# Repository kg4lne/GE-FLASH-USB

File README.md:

GE-Flash-USB X2212/X2444 EPROM Programmer
=========================================

This archive contains all the CAD and firmware files necessary to build the
GE-Flash-USB EPROM programmer for use with the GE-Flash programming software
by KG4LNE. GE-Flash is a complete solution for programming vintage GE Phoenix,
Delta and Ranger VHF/UHF commercial radios. For more information, please visit
the website at http://www.rtzaudio.com/kg4lne for additional information.

This package includes all PCB CAD files and firmware C source code. All PCB CAD
files are in Cadsoft Eagle v6.4.0 format. The source code for the AT90USB firmware
was developed in Atmel Studio 6.1 and was originally adapted from the USBKEY sample
provided by Atmel. I modified this from a mass storage device into to a simple
read/write USB device. The simple USB device can be accessed on Windows 7/8 via
the built-in generic WinUSB interface that ships with Windows.

You will need to install and configure your GE-Flash-USB programmer device to
communicate with WinUSB just like any other device though. The GE-Flash-USB driver
install and INF files are located on my website and are included in the 
GE-Flash application installer also. Be sure and have the INF and other driver
files on your machine (or install the GE-Flash application first). You can let
Windows search the GE-Flash program files application directory for the INF
file as well.

Note the BOM files for the programmer PCB are located in the project BOM 
subdirectory, here you'll also find an order upload file
"GEF-USB-B_OrderUploadDigiKey.csv" that can be uploaded to Digikey.
Upload the parts order file using the Digikey BOM manager in your account,
this will preload an order with all parts needed to build the PCB. 

Enjoy!

KG4LNE

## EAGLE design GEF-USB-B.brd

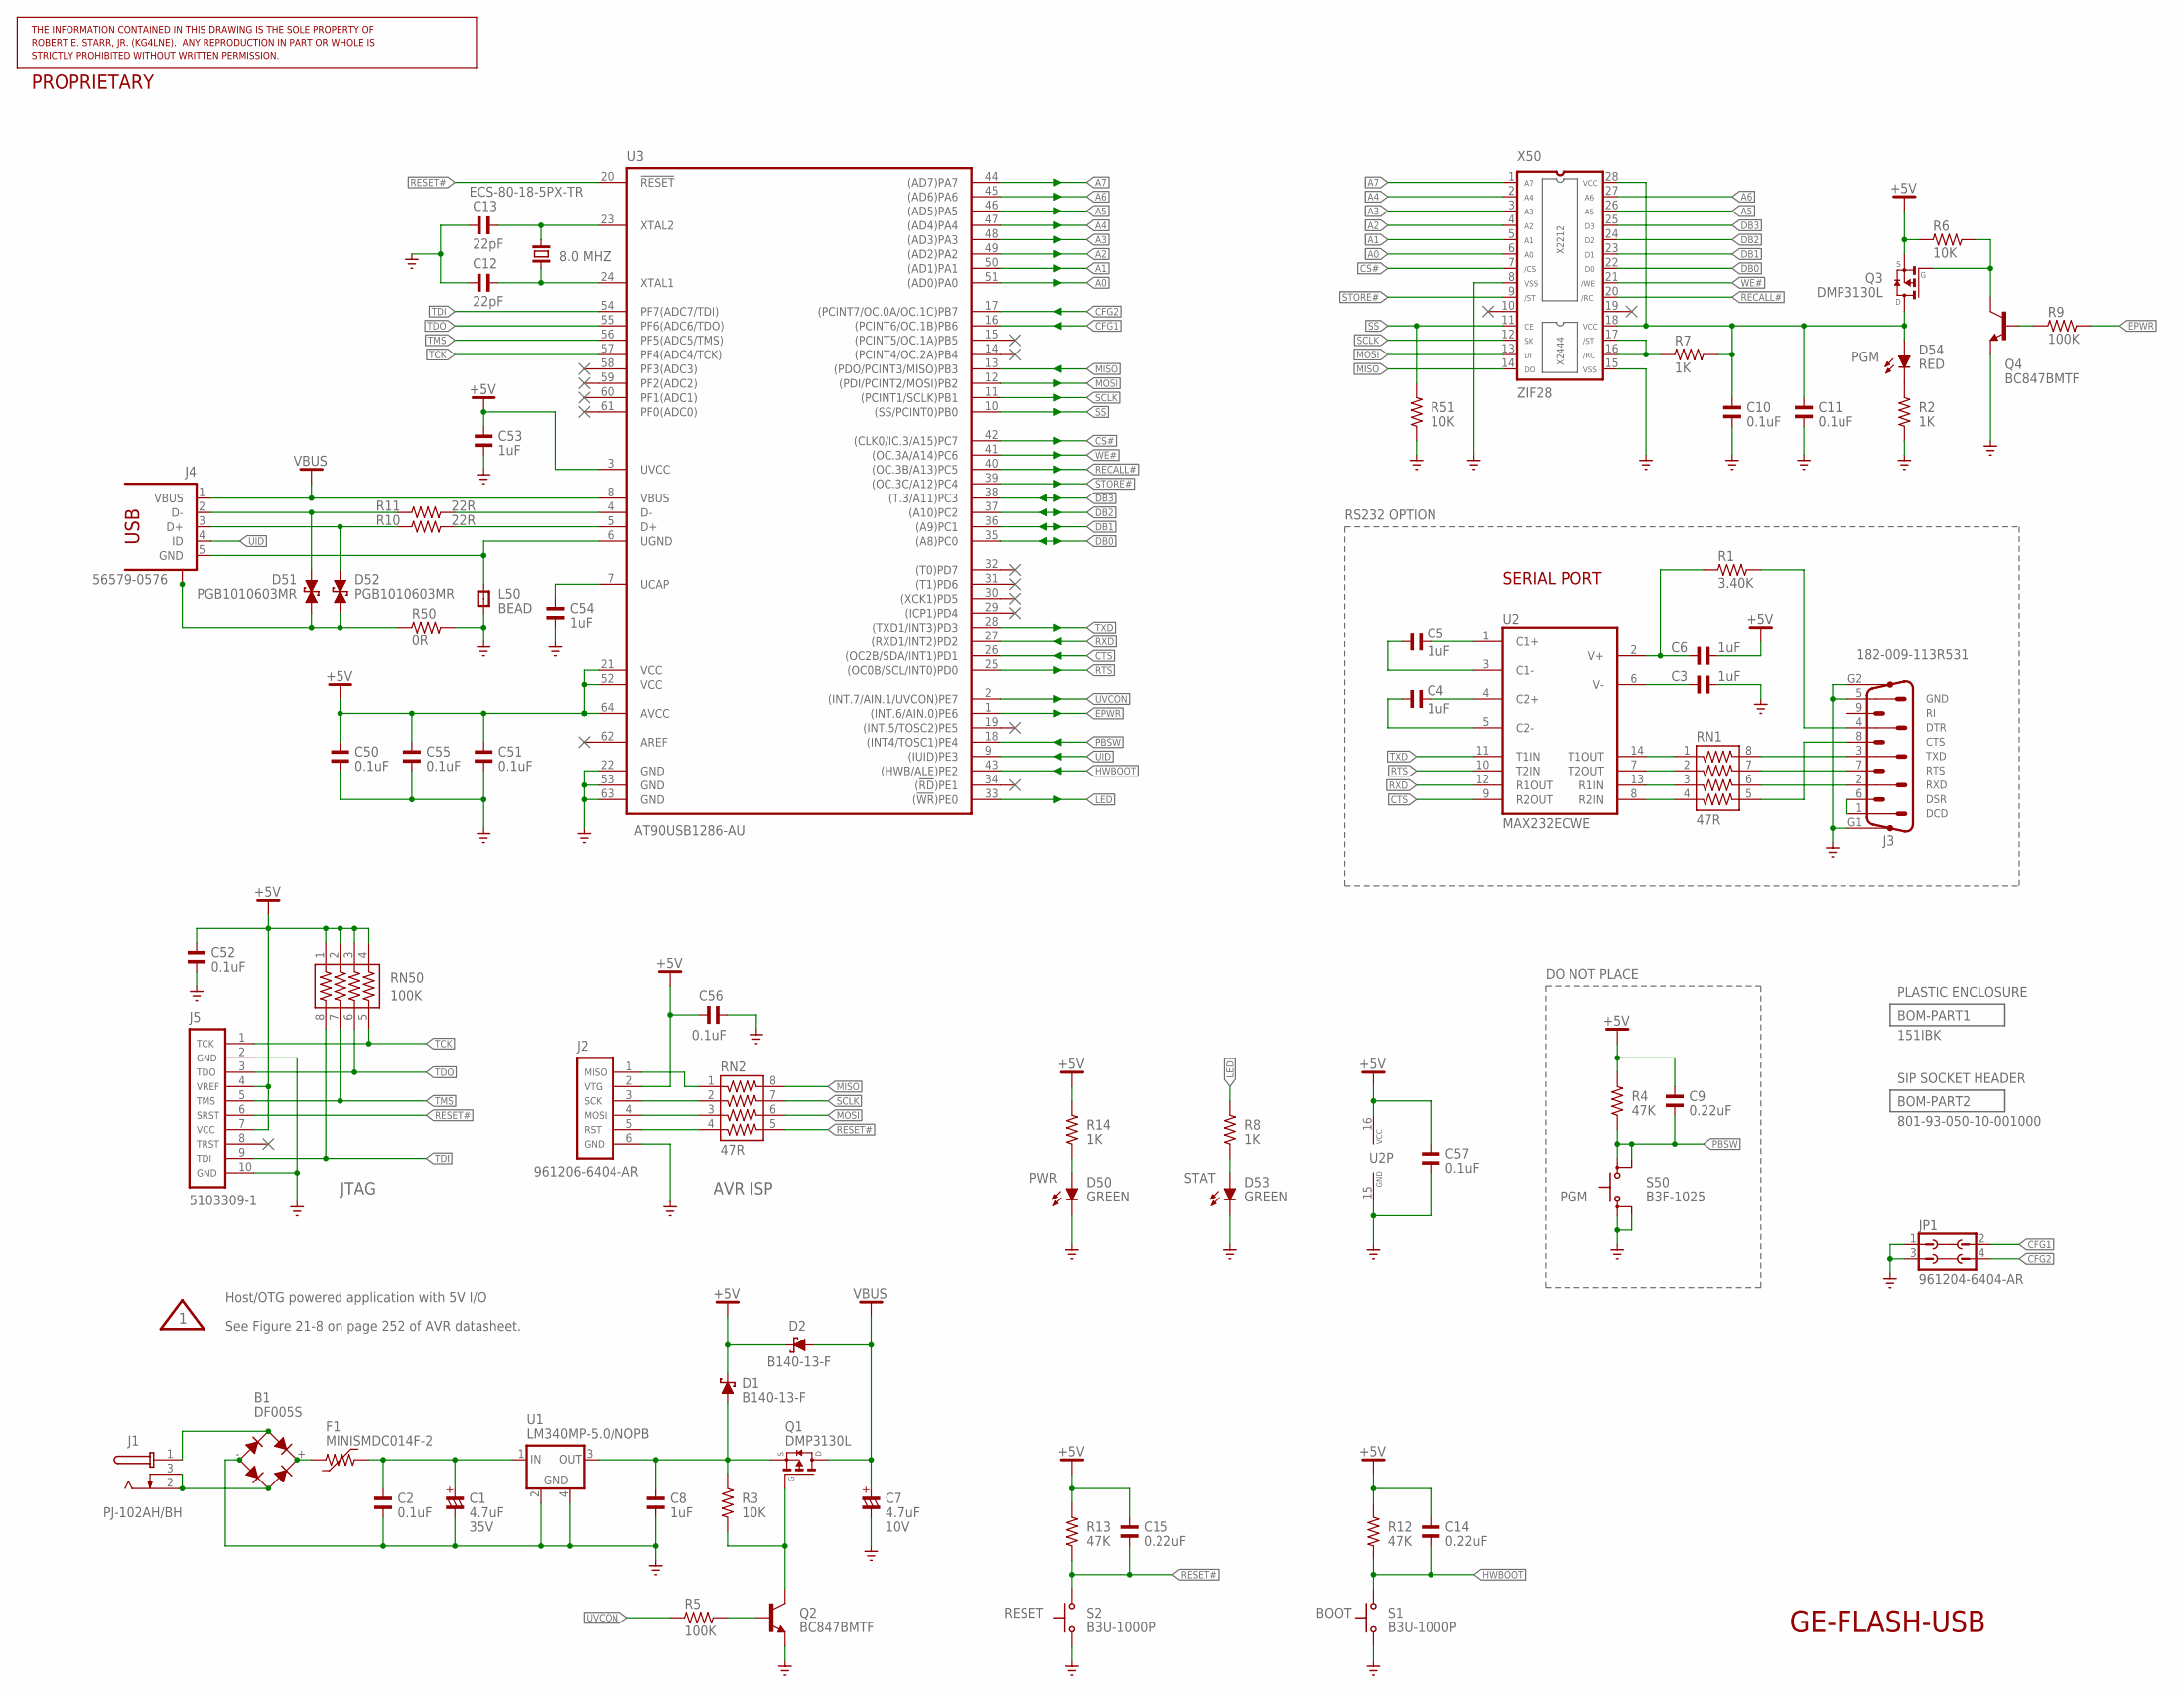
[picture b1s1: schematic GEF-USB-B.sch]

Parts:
B1: DF005S; DF-S; PARTNO DF005S
C1: 4.7uF; C7343/T; PARTNO TAJD475M035RNJ
C2, C10, C11, C50, C51, C52, C55, C56, C57: 0.1uF; C0805; PARTNO GCM21BR72A104KA37L
C3, C4, C5, C6, C8, C53, C54: 1uF; C0805; PARTNO GCM21BR71E105KA56L
C7: 4.7uF; C3528/T; PARTNO TAJB475K010RNJ
C9, C14, C15: 0.22uF; C0805; PARTNO GCM21BR71H224KA37L
C12, C13: 22pF; C0805; PARTNO GRM2195C2A220JZ01D
D1, D2: B140-13-F; SMA; PARTNO B140-13-F
D50, D53: GREEN; LED3MM; PARTNO TLHG4405
D51, D52: PGB1010603MR; PGB-0603; PARTNO PGB1010603MR
D54: RED; LED3MM; PARTNO TLHR4405
F1: MINISMDC014F-2; F1812; PARTNO MINISMDC014F-2
J1: PJ-102AH/BH; PJ-102XH; PARTNO PJ-102AH
J2: 961206-6404-AR; HDR-MA03-2; PARTNO 961206-6404-AR
J3: 182-009-113R531; NC182M9; PARTNO 182-009-113R531
J4: 56579-0576; PARTNO 56579-0576
J5: 5103309-1; HDR-5103309-1; PARTNO 5103309-1
JP1: 961204-6404-AR; JP2Q; PARTNO 961204-6404-AR
L50: BEAD; L0805; PARTNO BLM21PG221SN1D
Q1, Q3: DMP3130L; SOT23; PARTNO DMP3130L
Q2, Q4: BC847BMTF; SOT23; PARTNO BC847BMTF
R1: 3.40K; R0805; PARTNO ERJ-6ENF3401V
R2, R7, R8, R14: 1K; R0805; PARTNO ERJ-6ENF1001V
R3, R6, R51: 10K; R0805; PARTNO ERJ-6ENF1022V
R4, R12, R13: 47K; R0805; PARTNO ERJ-6ENF4702V
R5, R9: 100K; R0805; PARTNO ERJ-6ENF1003V
R10, R11: 22R; R0805; PARTNO ERJ-6ENF22R1V
R50: 0R; R0805; PARTNO ERJ-6GEY0R00V
RN1, RN2: 47R; 744-8; PARTNO 744C083470JTR
RN50: 100K; 744-8; PARTNO 744C083104JPTR
S1, S2: B3U-1000P; PARTNO B3U-1000P
S50: B3F-1025; B3F-10XX-B; PARTNO B3F-1025
U1: LM340MP-5.0/NOPB; SOT223; PARTNO LM340MP-5.0/NOPB
U2: MAX232ECWE; SO16W; PARTNO MAX232ECWE+
U3: AT90USB1286-AU; TQFP64A; PARTNO AT90USB1286-AU
X50: ZIF28; PARTNO 28-6554-11
Y1: 8.0 MHZ; HC49UP; PARTNO ECS-80-18-5PX-TR

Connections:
+5V: C6.1, C9.2, C14.2, C15.2, C50.1, C51.2, C52.1, C53.2, C55.1, C56.2, C57.1, D1.C, D2.C, J2.2, J5.4, J5.7, Q3.2 (S), R4.2, R6.1, R12.2, R13.2, R14.2, RN50.1, RN50.2, RN50.3, RN50.4, U2.16 (VCC), U3.3 (UVCC), U3.21 (VCC), U3.52 (VCC), U3.64 (AVCC)
A0: U3.51 ((AD0)PA0), X50.6
A1: U3.50 ((AD1)PA1), X50.5
A2: U3.49 ((AD2)PA2), X50.4
A3: U3.48 ((AD3)PA3), X50.3
A4: U3.47 ((AD4)PA4), X50.2
A5: U3.46 ((AD5)PA5), X50.26
A6: U3.45 ((AD6)PA6), X50.27
A7: U3.44 ((AD7)PA7), X50.1
CFG1: JP1.2, U3.16 ((PCINT6/OC.1B)PB6)
CFG2: JP1.4, U3.17 ((PCINT7/OC.0A/OC.1C)PB7)
CS#: U3.42 ((CLK0/IC.3/A15)PC7), X50.7
CTS: U2.9 (R2OUT), U3.26 ((OC2B/SDA/INT1)PD1)
DB0: U3.35 ((A8)PC0), X50.22
DB1: U3.36 ((A9)PC1), X50.23
DB2: U3.37 ((A10)PC2), X50.24
DB3: U3.38 ((T.3/A11)PC3), X50.25
EPWR: R9.2, U3.1 ((INT.6/AIN.0)PE6)
GND: B1.-, C1.-, C2.1, C3.1, C7.-, C8.2, C10.1, C11.1, C12.1, C13.1, C50.2, C51.1, C52.2, C53.1, C54.1, C55.2, C56.1, C57.2, D50.K (C), D53.K (C), J2.6, J3.5, J3.G1, J3.G2, J5.2, J5.10, JP1.1, JP1.3, L50.1, Q2.2 (E), Q4.2 (E), R2.1, R50.2, R51.1, S1.1, S2.1, S50.3, S50.4 (P1), U1.2 (GND), U1.4 (GND1), U2.15 (GND), U3.22 (GND), U3.53 (GND), U3.63 (GND), X50.8, X50.15
HWBOOT: C14.1, R12.1, S1.2 (S), U3.43 ((HWB/ALE)PE2)
LED: R8.2, U3.33 ((!WR!)PE0)
MISO: RN2.8, U3.13 ((PDO/PCINT3/MISO)PB3), X50.14
MOSI: RN2.6, U3.12 ((PDI/PCINT2/MOSI)PB2), X50.13
unnamed: J2.5, RN2.4
unnamed: B1.AC2 (A2), J1.2 (S), J1.3 (SS)
unnamed: R10.2, U3.5 (D+)
unnamed: D52.2, J4.3 (D+), R10.1
unnamed: R11.2, U3.4 (D-)
unnamed: D51.2, J4.2 (D-), R11.1
unnamed: C54.2, U3.7 (UCAP)
unnamed: D50.A, R14.1
unnamed: D51.1, D52.1, J4.S1, J4.S2, J4.S3, J4.S4, R50.1
unnamed: D53.A, R8.1
unnamed: Q1.1 (G), Q2.3 (C), R3.1
unnamed: Q2.1 (B), R5.2
unnamed: Q3.1 (G), Q4.3 (C), R6.2
unnamed: C10.2, C11.2, D54.A, Q3.3 (D), R7.2, X50.18, X50.28
unnamed: D54.K (C), R2.2
unnamed: J4.5 (GND), L50.2, U3.6 (UGND)
unnamed: J3.1, J3.6
unnamed: C1.+, C2.2, F1.2, U1.1 (IN)
unnamed: C8.1, D1.A, Q1.2 (S), R3.2, U1.3 (OUT)
unnamed: J3.2, RN1.6
unnamed: B1.+, F1.1
unnamed: B1.AC1 (A1), J1.1 (T)
unnamed: Q4.1 (B), R9.1
unnamed: C12.2, U3.24 (XTAL1), Y1.1
unnamed: J3.7, RN1.7
unnamed: C3.2, U2.6 (V-)
unnamed: C6.2, R1.1, U2.2 (V+)
unnamed: C13.2, U3.23 (XTAL2), Y1.2
unnamed: C4.1, U2.4 (C2+)
unnamed: C5.1, U2.1 (C1+)
unnamed: C4.2, U2.5 (C2-)
unnamed: C5.2, U2.3 (C1-)
unnamed: J3.8, RN1.5
unnamed: J3.3, RN1.8
unnamed: RN1.3, U2.13 (R1IN)
unnamed: RN1.1, U2.14 (T1OUT)
unnamed: RN1.4, U2.8 (R2IN)
unnamed: J3.4, R1.2
unnamed: RN1.2, U2.7 (T2OUT)
unnamed: J2.1, RN2.1
unnamed: J2.3, RN2.2
unnamed: J2.4, RN2.3
PBSW: C9.1, R4.1, S50.1 (S), S50.2 (S1), U3.18 ((INT4/TOSC1)PE4)
PU2: R7.1, X50.16, X50.17
RECALL#: U3.40 ((OC.3B/A13)PC5), X50.20
RESET#: C15.1, J5.6, R13.1, RN2.5, S2.2 (S), U3.20 (!RESET!)
RTS: U2.10 (T2IN), U3.25 ((OC0B/SCL/INT0)PD0)
RXD: U2.12 (R1OUT), U3.27 ((RXD1/INT2)PD2)
SCLK: RN2.7, U3.11 ((PCINT1/SCLK)PB1), X50.12
SS: R51.2, U3.10 ((SS/PCINT0)PB0), X50.11
STORE#: U3.39 ((OC.3C/A12)PC4), X50.9
TCK: J5.1, RN50.5, U3.57 (PF4(ADC4/TCK))
TDI: J5.9, RN50.8, U3.54 (PF7(ADC7/TDI))
TDO: J5.3, RN50.6, U3.55 (PF6(ADC6/TDO))
TMS: J5.5, RN50.7, U3.56 (PF5(ADC5/TMS))
TXD: U2.11 (T1IN), U3.28 ((TXD1/INT3)PD3)
UID: J4.4 (ID), U3.9 ((IUID)PE3)
UVCON: R5.1, U3.2 ((INT.7/AIN.1/UVCON)PE7)
VBUS: C7.+, D2.A, J4.1 (VBUS), Q1.3 (D), U3.8 (VBUS)
WE#: U3.41 ((OC.3A/A14)PC6), X50.21

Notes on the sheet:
AVR ISP
JTAG
See Figure 21-8 on page 252 of AVR datasheet.
Host/OTG powered application with 5V I/O
VCC
/WE
/ST
/RC
/CS
VSS
X2444
X2212
SERIAL PORT
DCD
DSR
RXD
RTS
TXD
CTS
DTR
GND
GE-FLASH-USB
DO NOT PLACE
RS232 OPTION

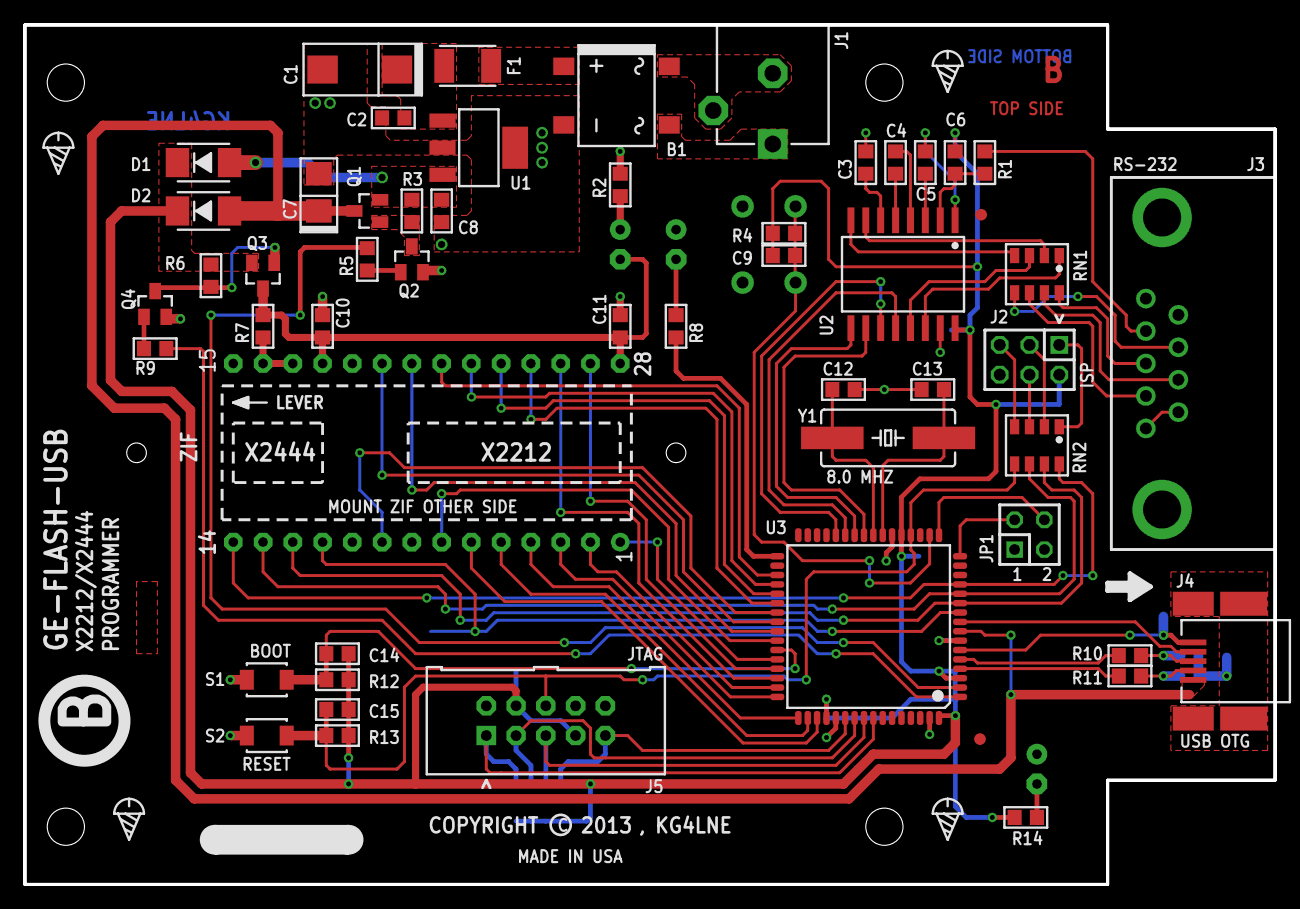
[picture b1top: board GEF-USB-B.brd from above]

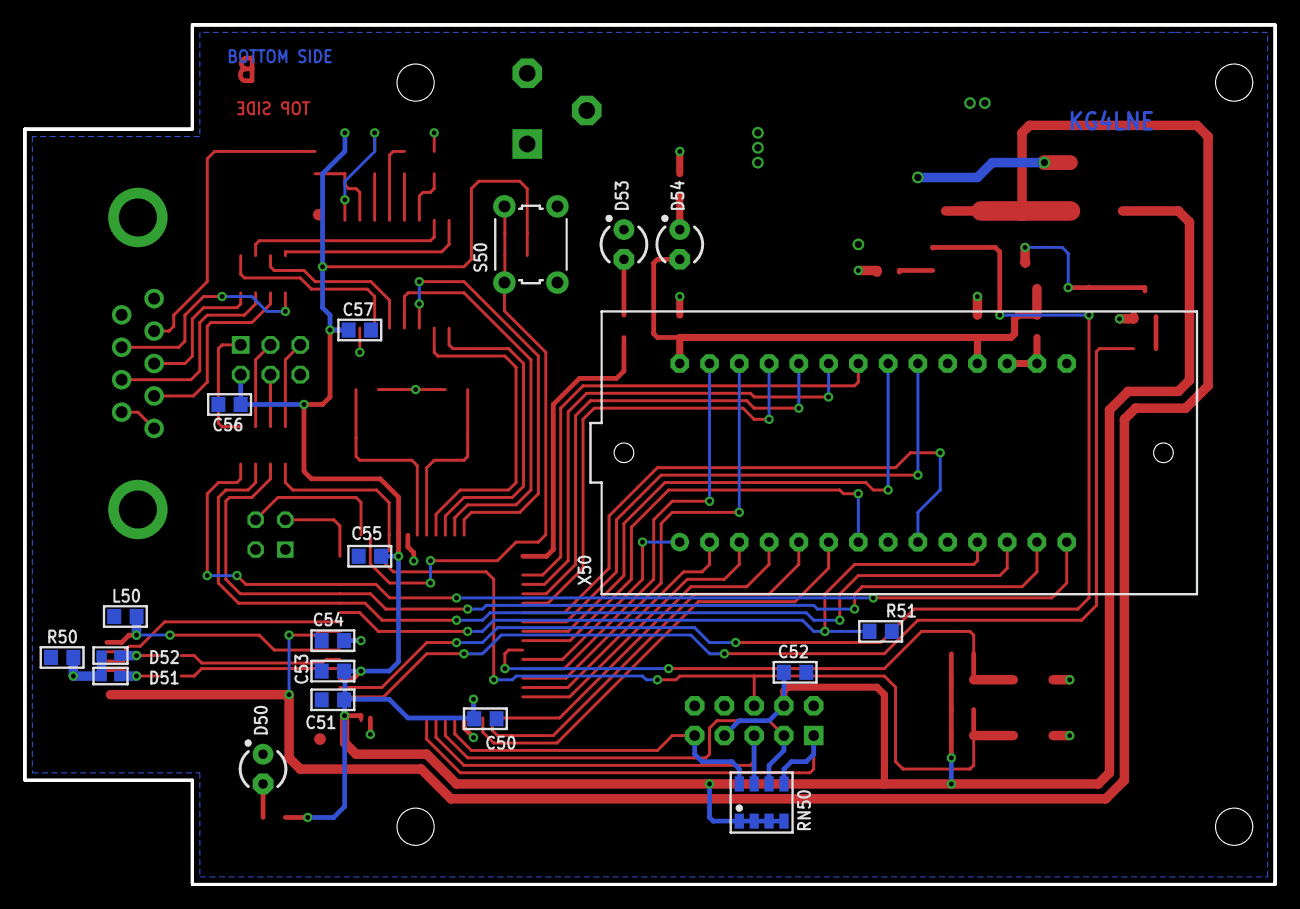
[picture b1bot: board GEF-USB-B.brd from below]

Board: 2 copper layers, 106.7 x 73.3 mm, 86 parts (19 on the bottom side), 83 nets.

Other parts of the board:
FABFRAME1: FAB_FRAME_ANSI-A
FABFRAME2: FAB_DOCFIELD_GENERIC
FEAT1, FEAT3, FEAT11, FEAT12: ICON_SCREW-S
FEAT2: PCBFEAT-MREV-076
FEAT4, FEAT9: G10
FEAT5, FEAT10: ICON_PIN1_A
FEAT6: ICON_ARROW-S
FEAT7: PCBFEAT-DATECODE-050R
FEAT8: PCBFEAT-REV-150
FEAT13: PCBFEAT-COPYRIGHT-050
FEAT14: FIELD_SCRIBBLE-1

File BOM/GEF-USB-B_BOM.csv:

Qty,Part References,Value,Package,Mfg Part Num,Mfg Name,VID,Vendor Part Num,Description,XREF
9,"C2, C10, C11, C50, C51, C52, C55, C56, C57",0.1uF,C0805,GCM21BR72A104KA37L,Murata Electronics,DK,490-4789-1-ND,CAP CER .1UF 100V X7R 0805,REF24
3,"C9(DNP), C14, C15",0.22uF,C0805,GCM21BR71H224KA37L,Murata Electronics,DK,490-4970-1-ND,CAP CER .22UF 50V X7R 0805,REF26
1,R50,0R,R0805,ERJ-6GEY0R00V,Panasonic - ECG,DK,P0.0ACT-ND,RES 0.0 OHM 1/8W 0805 SMD,REF29
4,"R2, R7, R8, R14",1K,R0805,ERJ-6ENF1001V,Panasonic - ECG,DK,P1.00KCCT-ND,RES 1.00K OHM 1/8W 1% 0805 SMD,REF30
7,"C3, C4, C5, C6, C8, C53, C54",1uF,C0805,GCM21BR71E105KA56L,Murata Electronics,DK,490-4785-1-ND,CAP CER 1UF 25V X7R 0805,REF27
1,R1,3.40K,R0805,ERJ-6ENF3401V,Panasonic - ECG,DK,P3.40KCCT-ND,RES 3.40K OHM 1/8W 1% 0805 SMD,REF31
1,C7,4.7uF,C3528/T,TAJB475K010RNJ,AVX Corporation,DK,478-3886-1-ND,CAP TANTALUM 4.7UF 10V 10% SMD,REF23
1,C1,4.7uF,C7343/T,TAJD475M035RNJ,AVX Corporation,DK,478-3934-1-ND,CAP TANTALUM 4.7UF 35V 20% SMD,REF22
1,Y1,8.0 MHZ,HC49UP,ECS-80-18-5PX-TR,ECS Inc,DK,XC1271CT-ND,CRYSTAL 8.00MHZ 18PF SMD,REF17
3,"R3, R6, R51",10K,R0805,ERJ-6ENF1022V,Panasonic - ECG,DK,P10.2KCCT-ND,RES 10.2K OHM 1/8W 1% 0805 SMD,REF32
2,"R10, R11",22R,R0805,ERJ-6ENF22R1V,Panasonic - ECG,DK,P22.1CCT-ND,RES 22.1 OHM 1/8W 1% 0805 SMD,REF33
2,"C12, C13",22pF,C0805,GRM2195C2A220JZ01D,Murata Electronics,DK,490-1591-1-ND,CAP CER 22PF 100V 5% C0G 0805,REF25
3,"R4(DNP), R12, R13",47K,R0805,ERJ-6ENF4702V,Panasonic - ECG,DK,P47.0KCCT-ND,RES 47.0K OHM 1/8W 1% 0805 SMD,REF35
2,"RN1, RN2",47R,744-8,744C083470JTR,CTS Resistor Products,DK,744C083470JPCT-ND,RES ARRAY 47 OHM 8TERM 4RES SMD,REF20
1,RN50,100K,744-8,744C083104JPTR,CTS Resistor Products,DK,744C083104JPCT-ND,RES ARRAY 100KOHM 8TERM 4RES SMD,REF21
2,"R5, R9",100K,R0805,ERJ-6ENF1003V,Panasonic - ECG,DK,P100KCCT-ND,RES 100K OHM 1/8W 1% 0805 SMD,REF36
1,BOM-PART1,151IBK,*,151IBK,Serpac,DK,SR151-IB-ND,PLASTIC ENCLOSURE 5.62X3.25X1.50 BLACK,REF39
1,J3,182-009-113R531,NC182M9,182-009-113R531,Norcomp Inc.,DK,182-09ME-ND,CONN DB9 MALE .318 R/A NICKEL,REF15
1,BOM-PART2,801-93-050-10-001000,*,801-93-050-10-001000,Mill-Max Mfg Corp,DK,ED7150-ND,SIP SOCKET 50 POS STRAIGHT PCB,REF40
1,J4,56579-0576,56579-0576,56579-0576,Molex Inc,DK,WM17122CT-ND,CONN RECEPT USB 5POS RT ANG SMD,REF14
1,JP1,961204-6404-AR,JP2Q,961204-6404-AR,3M,DK,3M9458-ND,CONN HEADER VERT DUAL 4POS GOLD,REF42
1,J2,961206-6404-AR,HDR-MA03-2,961206-6404-AR,3M,DK,3M9459-ND,CONN HEADER VERT DUAL 6POS GOLD,REF43
1,J5,5103309-1,HDR-5103309-1,5103309-1,Tyco Electronics,DK,A33160-ND,CONN HEADER LOPRO STR 10POS GOLD,REF16
1,U3,AT90USB1286-AU,TQFP64A,AT90USB1286-AU,Atmel,DK,AT90USB1286-AURCT-ND,MCU AVR 64K FLASH 16MHZ 64TQFP,REF2
1,S50(DNP),B3F-1025,B3F-10XX-B,B3F-1025,Omron Electronics Inc,DK,SW794-ND,SWITCH TACT 6MM 260GF H=5.0MM,REF11
2,"S1, S2",B3U-1000P,B3U-1000P,B3U-1000P,Omron Electronics Inc,DK,SW1020CT-ND,SWITCH TACT SPST W/O GND SMD,REF12
2,"D1, D2",B140-13-F,SMA,B140-13-F,Diodes Inc,DK,B140-FDICT-ND,DIODE SCHOTTKY 40V 1A SMA,REF38
2,"Q2, Q4",BC847BMTF,SOT23,BC847BMTF,Fairchild Semiconductor,DK,BC847BMTFCT-ND,TRANSISTOR NPN 45V 0.1A SOT23,REF4
1,L50,BEAD,L0805,BLM21PG221SN1D,Murata Electronics,DK,490-1054-1-ND,FERRITE CHIP 220 OHM 2000MA 0805,REF28
1,B1,DF005S,DF-S,DF005S,Fairchild Semiconductor,DK,DF005SCT-ND,DIODE BRIDGE 50V 1.5A 4-SDIP,REF5
2,"Q1, Q3",DMP3130L,SOT23,DMP3130L,Diodes Inc,DK,DMP3130LDICT-ND,MOSFET P-CH 30V 3.5A SOT-23,REF6
2,"D50, D53",GREEN,LED3MM,TLHG4405,Vishay Semiconductor,DK,751-1101-ND,LED 3MM GREEN 15MCD GAP ON GAP,REF10
1,U1,LM340MP-5.0/NOPB,SOT223,LM340MP-5.0/NOPB,National Semiconductor,DK,LM340MP-5.0/NOPBCT-ND,IC REG LDO 5V 1A SOT223,REF7
1,U2,MAX232ECWE,SO16W,MAX232ECWE+,Maxim Integrated Products,DK,MAX232ECWE+-ND,IC TXRX RS232 5V ESD-PROT 16SOIC,REF8
1,F1,MINISMDC014F-2,F1812,MINISMDC014F-2,Tyco Electronics,DK,MINISMDC014FCT-ND,POLYSWITCH .14A RESET FUSE SMD,REF19
2,"D51, D52",PGB1010603MR,PGB-0603,PGB1010603MR,Littelfuse Inc,DK,F2594CT-ND,SUPPRESSOR ESD 24VDC 0603 SMD,REF18
1,J1,PJ-102AH/BH,PJ-102XH,PJ-102AH,CUI Inc,DK,CP-102AH-ND,CONN PWR JACK 2.1X5.5MM HIGH CUR,REF13
1,D54,RED,LED3MM,TLHR4405,Vishay Semiconductor,DK,751-1129-ND,LED 3MM RED 15MCD GAASP ON GAP,REF9
1,X50,ZIF28,ZIF28,28-6554-11,Aries Electronics,DK,A303-ND,28 PIN ZIF SOCKET GOLD,REF41

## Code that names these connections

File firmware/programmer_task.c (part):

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#endif
    _NOP();
	
    /* PC4-PC7=output,PC0-PC3 are input */
    DDRC  = _BV(B_CS) | _BV(B_WE) | _BV(B_RECALL) | _BV(B_STORE);
    delay_ms(10);

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#endif
    _NOP();
	
    /* Set PC0-PC7 to all outputs */
    DDRC  = 0xFF;
    delay_ms(10);

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{
    /* PORT-A
     *
     * PA7  = AD7       (out)
     * PA6  = AD6       (out)
     * PA5  = AD5       (out)
     * PA4  = AD4       (out)
     * PA3  = AD3       (out)
     * PA2  = AD2       (out)
     * PA1  = AD1       (out)
     * PAO  = AD0       (out)
     */

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
    /* PORT-B
     *
     * PB7  = CFG2      (in:pullups enabled)
     * PB6  = CFG1      (in:pullups enabled)
     * PB5  = N/C       (in)
     * PB4  = N/C       (in)
     * PB3  = MISO      (in)
     * PB2  = MOSI      (out)
     * PB1  = SCLK      (out)
     * PBO  = SS        (out)
     */

    /* All pins to input */
    DDRB = 0;
    /* all pins low, pullups on PB6 & PB7 */
    PORTB = _BV(PB6) | _BV(PB7);
    _NOP();
    /* SS,SCLK,MOSI=output, all others are input */
    DDRB  = _BV(PB0) | _BV(PB1) | _BV(PB2);
    _NOP();

    /* Configure the SPI port for X2444 communication */
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
    /* PORT-C
     *
     * PC7  = CS#       (out)
     * PC6  = WE#       (out)
     * PC5  = RECALL#   (out)
     * PC4  = STORE#    (out)
     * PC3  = DB3       (i/o)
     * PC2  = DB2       (i/o)
     * PC1  = DB1       (i/o)
     * PCO  = DB0       (i/o)
     */

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    DDRC = 0;
    /* all pins low, no pullups */
    PORTC = 0x00;
    /* PC4-PC7=output, all others are input */
    DDRC  = _BV(PC4) | _BV(PC5) | _BV(PC6) | _BV(PC7);

    /* PORT-D
     *
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     * PD6  = N/C       (in)
     * PD5  = N/C       (in)
     * PD4  = N/C       (in)
     * PD3  = TXD       (out)
     * PD2  = RXD       (in)
     * PD1  = CTS       (in)
     * PDO  = RTS       (out)
     */

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    DDRD = 0;
    /* all pins low, no pullups */
    PORTD = 0x00;
    /* PD0,PE6,PE7=output, all others are input */
    DDRD  = _BV(PD0) | _BV(PD3);

    /* PORT-E
     *
     * PE7  = UVCON     (out)
     * PE6  = EPWR      (out)
     * PE5  = N/C       (in)
     * PE4  = PBSW      (in)
     * PE3  = UID       (in)
     * PE2  = HWBOOT    (in)
     * PE1  = N/C       (in)
     * PEO  = LED       (out)
     */
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    DDRE = 0;
    /* all pins low, no pullups */
    PORTE = 0x00;
    /* PE0,PE6,PE7=output, all others are input */
    DDRE  = _BV(PE0) | _BV(PE6) | _BV(PE7);
    _NOP();
	/* Make sure the EPROM power is OFF */	
#if (HARDWARE_REV >= 2)
    PORTE = 0;			/* [Rev-B]:Set EPWR low for EPROM power off! */
#else
    PORTE = _BV(PE6);   /* [Rev-A]:Set EPWR high for EPROM power off! */
#endif
    /* Read the configuration jumpers */
    //g_jumpers = PINB & (_BV(B_CFG1) | _BV(B_CFG2));
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
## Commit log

2013-08-06 Initial Release
2014-03-02 BOM updates

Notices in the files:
GEF-USB-B.brd:
COPYRIGHT: , KG4LNE
parts and their libraries:
dpcb-feature: Copyright Field
Set copyright by text with global attribute >COMPANY
bom: Copyright (C) 2010, Bob Starr
